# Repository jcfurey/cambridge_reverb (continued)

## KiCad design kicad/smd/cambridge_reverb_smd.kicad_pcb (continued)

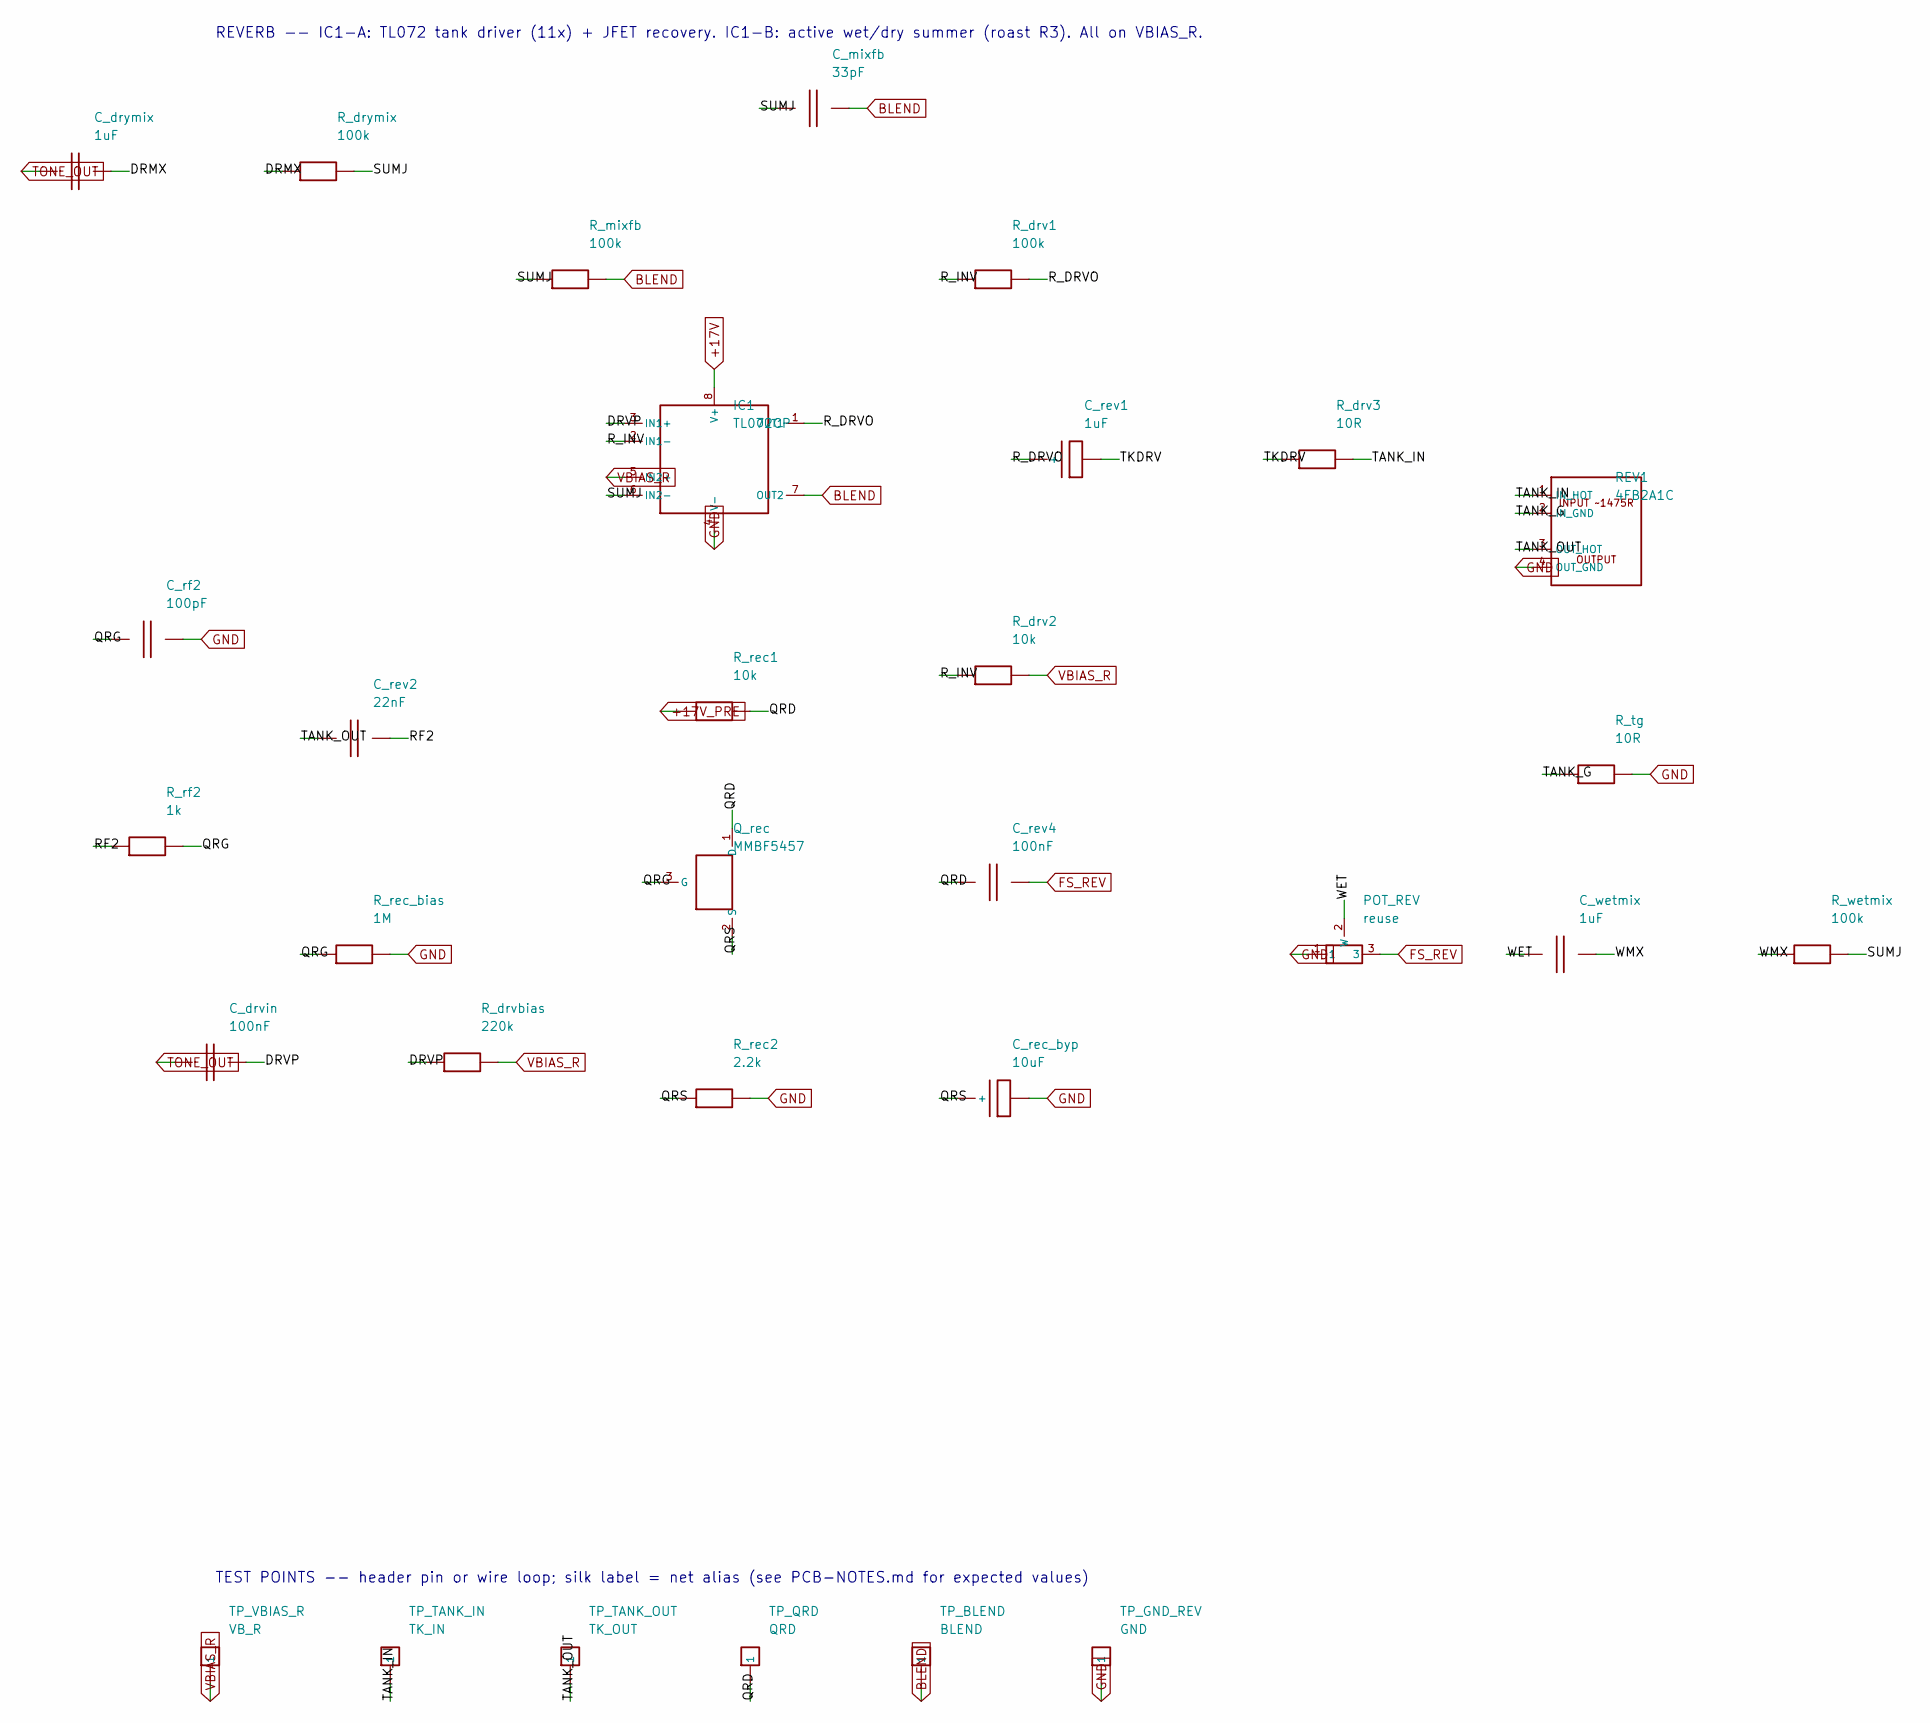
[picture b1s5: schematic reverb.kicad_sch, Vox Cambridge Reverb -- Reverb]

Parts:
C_drvin: 100nF; C_1206_3216Metric
C_drymix: 1uF; C_1206_3216Metric
C_mixfb: 33pF; C_0805_2012Metric
C_rec_byp: 10uF; CP_Radial_D5.0mm_P2.00mm
C_rev1: 1uF; CP_Radial_D5.0mm_P2.00mm
C_rev2: 22nF; C_1206_3216Metric
C_rev4: 100nF; C_1206_3216Metric
C_rf2: 100pF; C_0805_2012Metric
C_wetmix: 1uF; C_1206_3216Metric
IC1: TL072CP; DIP-8_W7.62mm
POT_REV: reuse; WirePad_1x03_P2.54mm_D1.2mm
Q_rec: MMBF5457; SOT-23
REV1: 4FB2A1C; WirePad_1x04_P2.54mm_D1.2mm
R_drv1: 100k; R_0805_2012Metric
R_drv2: 10k; R_0805_2012Metric
R_drv3: 10R; R_0805_2012Metric
R_drvbias: 220k; R_0805_2012Metric
R_drymix: 100k; R_0805_2012Metric
R_mixfb: 100k; R_0805_2012Metric
R_rec1: 10k; R_0805_2012Metric
R_rec2: 2.2k; R_Axial_DIN0207_L6.3mm_D2.5mm_P5.08mm_Vertical
R_rec_bias: 1M; R_0805_2012Metric
R_rf2: 1k; R_0805_2012Metric
R_tg: 10R; R_0805_2012Metric
R_wetmix: 100k; R_0805_2012Metric
TP_BLEND: BLEND; TestPoint_THT_D2.0mm_Label
TP_GND_REV: GND; TestPoint_THT_D2.0mm_Label
TP_QRD: QRD; TestPoint_THT_D2.0mm_Label
TP_TANK_IN: TK_IN; TestPoint_THT_D2.0mm_Label
TP_TANK_OUT: TK_OUT; TestPoint_THT_D2.0mm_Label
TP_VBIAS_R: VB_R; TestPoint_THT_D2.0mm_Label

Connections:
+17V: IC1.8 (V+); also elsewhere on the board
+17V_PRE: R_rec1.1; also elsewhere on the board
BLEND: C_mixfb.2, IC1.7 (OUT2), R_mixfb.2, TP_BLEND.1; also elsewhere on the board
DRMX: C_drymix.2, R_drymix.1
DRVP: C_drvin.2, IC1.3 (IN1+), R_drvbias.1
FS_REV: C_rev4.2, POT_REV.3; also elsewhere on the board
GND: C_rec_byp.2, C_rf2.2, IC1.4 (V-), POT_REV.1, REV1.4 (OUT_GND), R_rec2.2, R_rec_bias.2, R_tg.2, TP_GND_REV.1; also elsewhere on the board
QRD: C_rev4.1, Q_rec.1 (D), R_rec1.2, TP_QRD.1
QRG: C_rf2.1, Q_rec.3 (G), R_rec_bias.1, R_rf2.2
QRS: C_rec_byp.1 (+), Q_rec.2 (S), R_rec2.1
RF2: C_rev2.2, R_rf2.1
R_DRVO: C_rev1.1 (+), IC1.1 (OUT1), R_drv1.2
R_INV: IC1.2 (IN1-), R_drv1.1, R_drv2.1
SUMJ: C_mixfb.1, IC1.6 (IN2-), R_drymix.2, R_mixfb.1, R_wetmix.2
TANK_G: REV1.2 (IN_GND), R_tg.1
TANK_IN: REV1.1 (IN_HOT), R_drv3.2, TP_TANK_IN.1
TANK_OUT: C_rev2.1, REV1.3 (OUT_HOT), TP_TANK_OUT.1
TKDRV: C_rev1.2, R_drv3.1
TONE_OUT: C_drvin.1, C_drymix.1; also elsewhere on the board
VBIAS_R: IC1.5 (IN2+), R_drv2.2, R_drvbias.2, TP_VBIAS_R.1; also elsewhere on the board
WET: C_wetmix.1, POT_REV.2 (W)
WMX: C_wetmix.2, R_wetmix.1

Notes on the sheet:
REVERB -- IC1-A: TL072 tank driver (11x) + JFET recovery. IC1-B: active wet/dry summer (roast R3). All on VBIAS_R.
TEST POINTS -- header pin or wire loop; silk label = net alias (see PCB-NOTES.md for expected values)

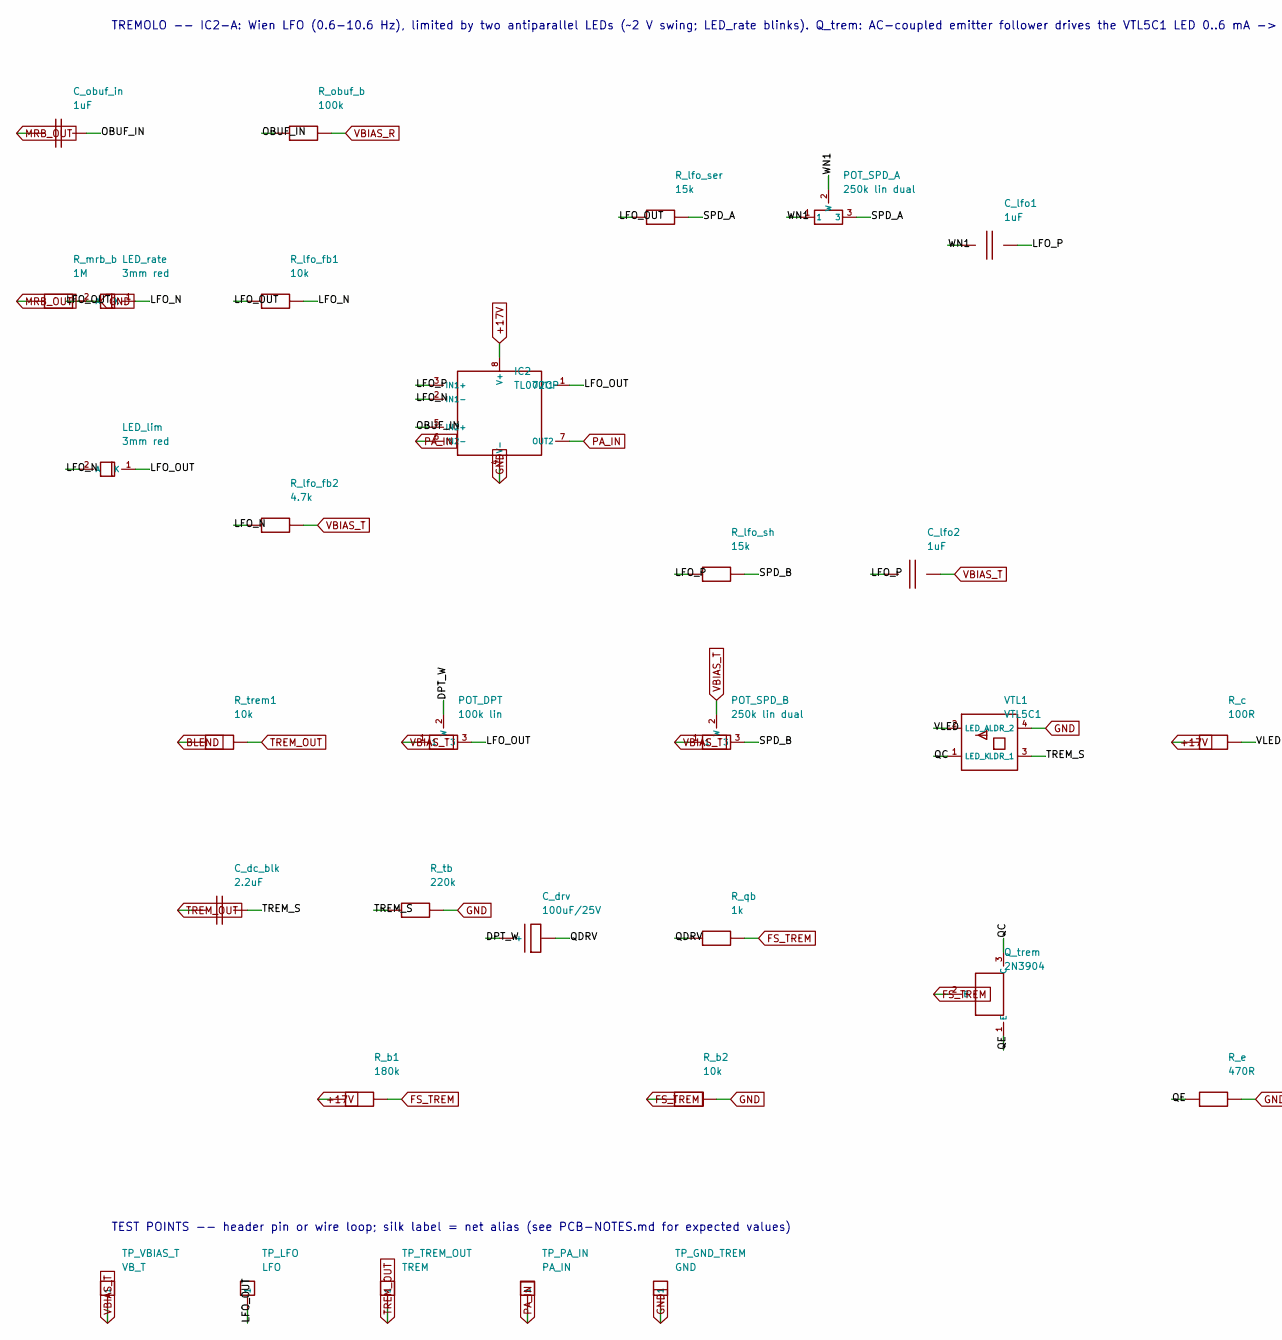
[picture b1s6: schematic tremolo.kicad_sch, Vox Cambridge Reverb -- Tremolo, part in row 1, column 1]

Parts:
C_dc_blk: 2.2uF; C_1206_3216Metric
C_drv: 100uF/25V; CP_Radial_D6.3mm_P2.50mm
C_lfo1, C_lfo2: 1uF; C_1206_3216Metric
C_obuf_in: 1uF; C_1206_3216Metric
IC2: TL072CP; DIP-8_W7.62mm
LED_lim: 3mm red; LED_D3.0mm
LED_rate: 3mm red; LED_D3.0mm
POT_DPT: 100k lin; WirePad_1x03_P2.54mm_D1.2mm
POT_SPD_A: 250k lin dual; WirePad_1x03_P2.54mm_D1.2mm
POT_SPD_B: 250k lin dual; WirePad_1x03_P2.54mm_D1.2mm
Q_trem: 2N3904; SOT-23_MMBT3904_as_EBC
R_b1: 180k; R_0805_2012Metric
R_b2: 10k; R_0805_2012Metric
R_c: 100R; R_0805_2012Metric
R_e: 470R; R_0805_2012Metric
R_lfo_fb1: 10k; R_0805_2012Metric
R_lfo_fb2: 4.7k; R_0805_2012Metric
R_lfo_ser: 15k; R_0805_2012Metric
R_lfo_sh: 15k; R_0805_2012Metric
R_mrb_b: 1M; R_0805_2012Metric
R_obuf_b: 100k; R_0805_2012Metric
R_qb: 1k; R_0805_2012Metric
R_tb: 220k; R_0805_2012Metric
R_trem1: 10k; R_0805_2012Metric
TP_GND_TREM: GND; TestPoint_THT_D2.0mm_Label
TP_LFO: LFO; TestPoint_THT_D2.0mm_Label
TP_PA_IN: PA_IN; TestPoint_THT_D2.0mm_Label
TP_TREM_OUT: TREM; TestPoint_THT_D2.0mm_Label
TP_VBIAS_T: VB_T; TestPoint_THT_D2.0mm_Label
VTL1: VTL5C1

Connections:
+17V: IC2.8 (V+), R_b1.1, R_c.1; also elsewhere on the board
BLEND: R_trem1.1; also elsewhere on the board
DPT_W: C_drv.1 (+), POT_DPT.2 (W)
FS_TREM: Q_trem.2 (B), R_b1.2, R_b2.1, R_qb.2; also elsewhere on the board
GND: IC2.4 (V-), R_b2.2, R_e.2, R_mrb_b.2, R_tb.2, TP_GND_TREM.1, VTL1.4 (LDR_2); also elsewhere on the board
LFO_N: IC2.2 (IN1-), LED_lim.2 (A), LED_rate.1 (K), R_lfo_fb1.2, R_lfo_fb2.1
LFO_OUT: IC2.1 (OUT1), LED_lim.1 (K), LED_rate.2 (A), POT_DPT.3, R_lfo_fb1.1, R_lfo_ser.1, TP_LFO.1
LFO_P: C_lfo1.2, C_lfo2.1, IC2.3 (IN1+), R_lfo_sh.1
MRB_OUT: C_obuf_in.1, R_mrb_b.1; also elsewhere on the board
OBUF_IN: C_obuf_in.2, IC2.5 (IN2+), R_obuf_b.1
PA_IN: IC2.6 (IN2-), IC2.7 (OUT2), TP_PA_IN.1; also elsewhere on the board
QC: Q_trem.3 (C), VTL1.1 (LED_K)
QDRV: C_drv.2, R_qb.1
QE: Q_trem.1 (E), R_e.1
SPD_A: POT_SPD_A.3, R_lfo_ser.2
SPD_B: POT_SPD_B.3, R_lfo_sh.2
TREM_OUT: C_dc_blk.1, R_trem1.2, TP_TREM_OUT.1; also elsewhere on the board
TREM_S: C_dc_blk.2, R_tb.1, VTL1.3 (LDR_1)
VBIAS_R: R_obuf_b.2; also elsewhere on the board
VBIAS_T: C_lfo2.2, POT_DPT.1, POT_SPD_B.1, POT_SPD_B.2 (W), R_lfo_fb2.2, TP_VBIAS_T.1; also elsewhere on the board
VLED: R_c.2, VTL1.2 (LED_A)
WN1: C_lfo1.1, POT_SPD_A.1, POT_SPD_A.2 (W)

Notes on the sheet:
TREMOLO -- IC2-A: Wien LFO (0.6-10.6 Hz), limited by two antiparallel LEDs (~2 V swing; LED_rate blinks). Q_trem: AC-coupled emitter follower drives the VTL5C1 LED 0..6 mA -> 15 dB depth, 0.8 dB insertion loss (was 7 mA DC: -20 dB pad, 1.7 dB depth). IC2-B: post-MRB output buffer -> PA_IN.
TEST POINTS -- header pin or wire loop; silk label = net alias (see PCB-NOTES.md for expected values)

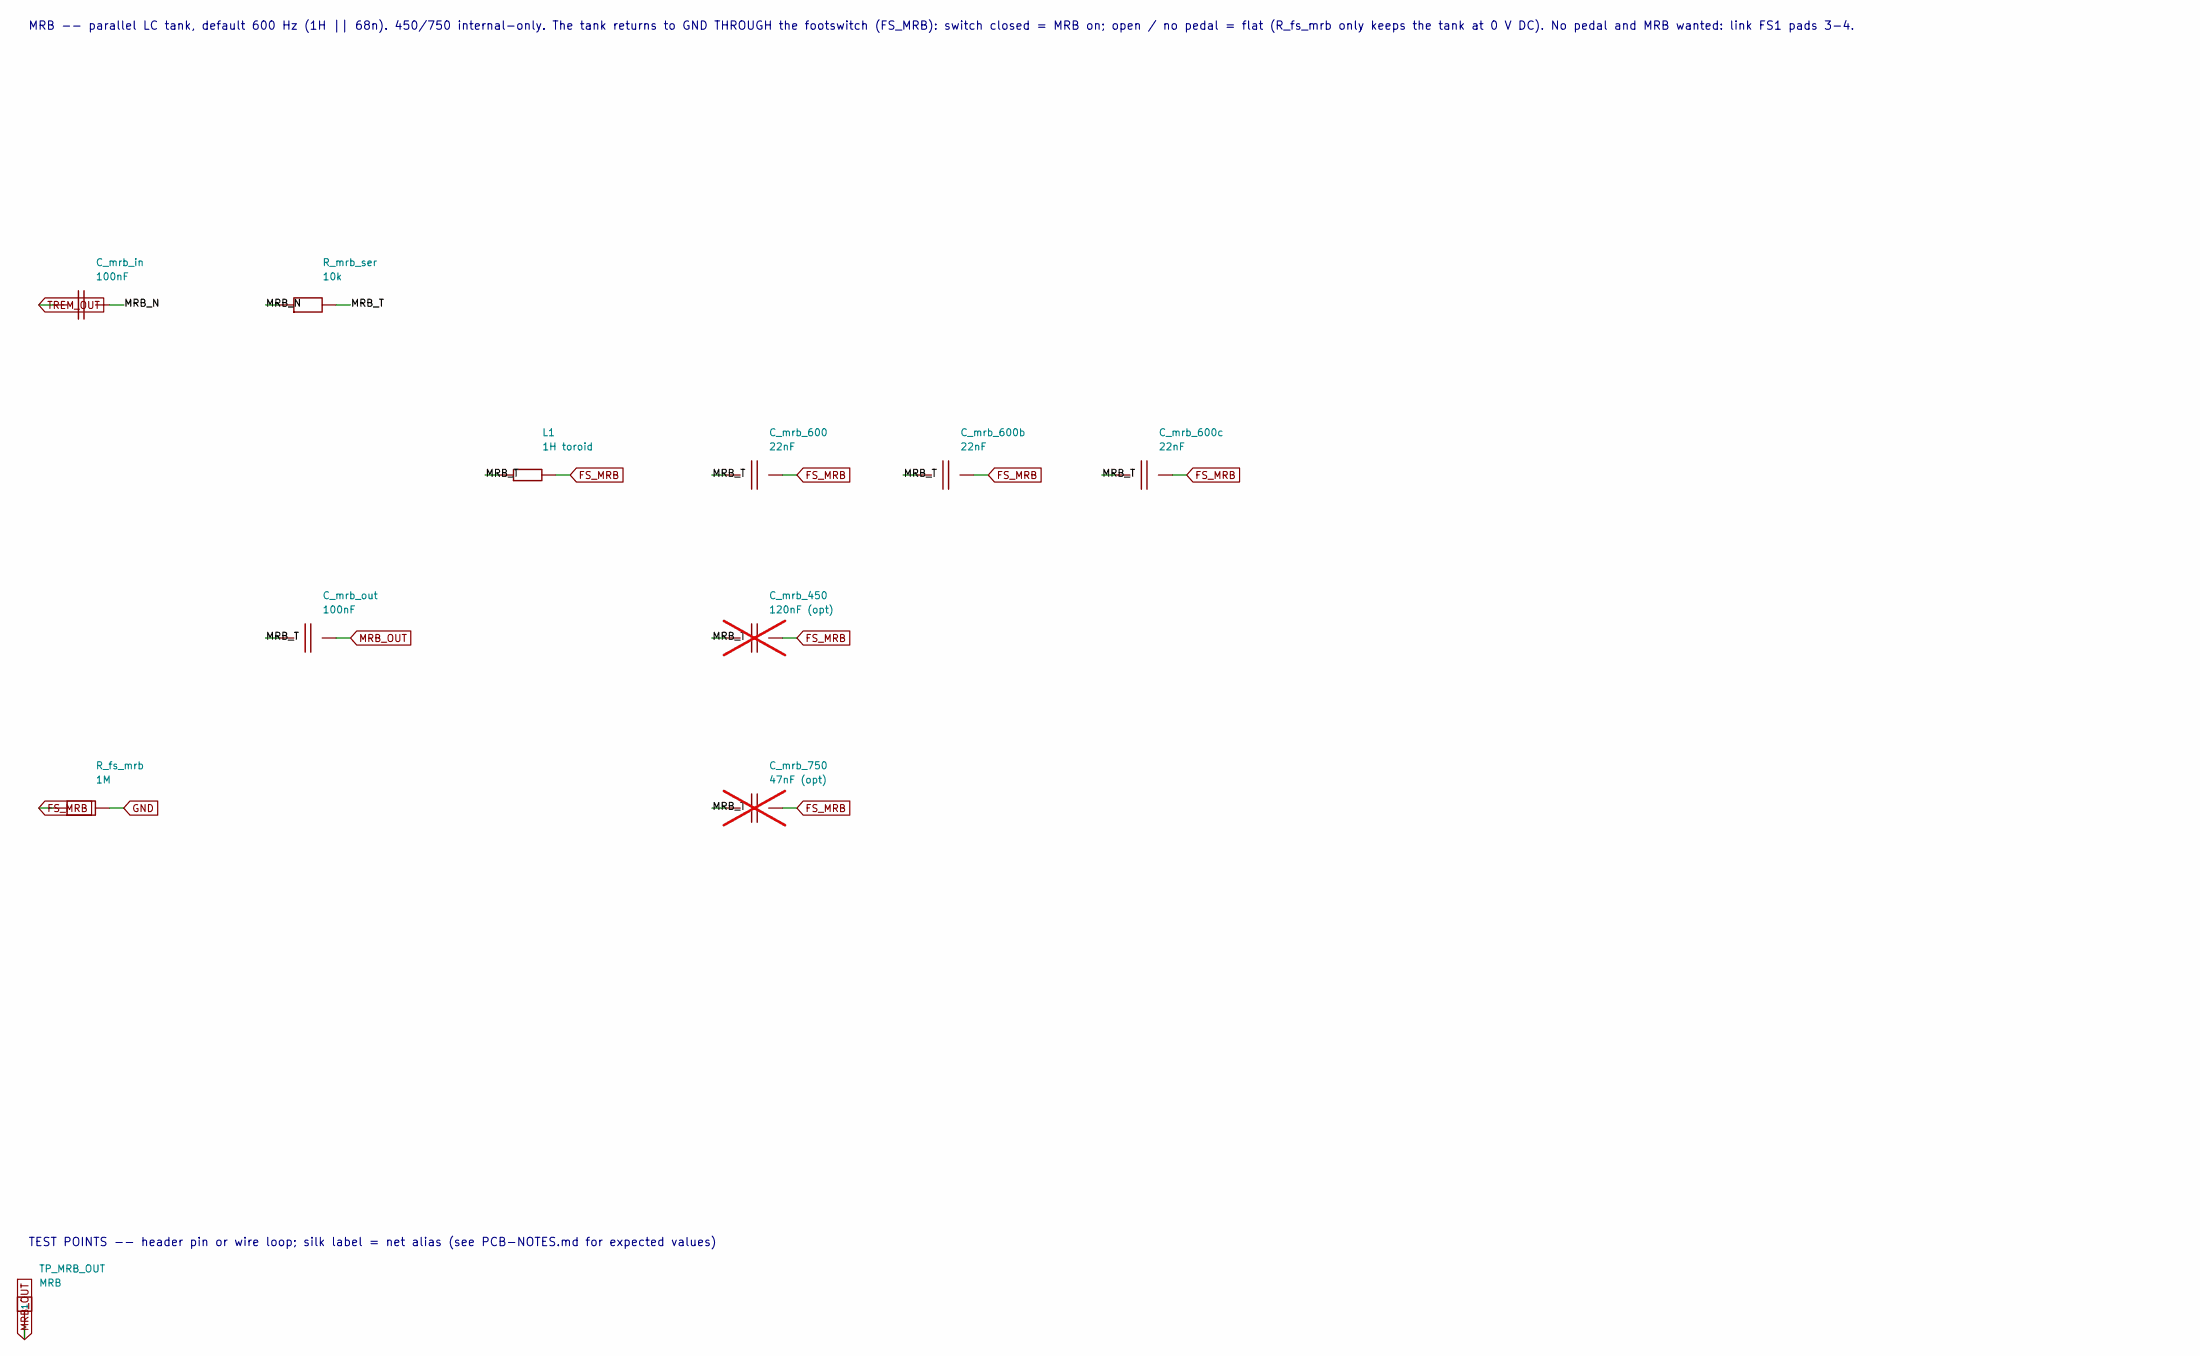
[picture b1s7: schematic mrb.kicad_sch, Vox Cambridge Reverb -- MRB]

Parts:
C_mrb_450: 120nF (opt); C_1206_3216Metric; not fitted
C_mrb_600, C_mrb_600b, C_mrb_600c: 22nF; C_1206_3216Metric
C_mrb_750: 47nF (opt); C_1206_3216Metric; not fitted
C_mrb_in: 100nF; C_1206_3216Metric
C_mrb_out: 100nF; C_1206_3216Metric
L1: 1H toroid; Inductor_MRB_1H_Toroid
R_fs_mrb: 1M; R_0805_2012Metric
R_mrb_ser: 10k; R_0805_2012Metric
TP_MRB_OUT: MRB; TestPoint_THT_D2.0mm_Label

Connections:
FS_MRB: C_mrb_450.2, C_mrb_600.2, C_mrb_600b.2, C_mrb_600c.2, C_mrb_750.2, L1.2, R_fs_mrb.1; also elsewhere on the board
GND: R_fs_mrb.2; also elsewhere on the board
MRB_N: C_mrb_in.2, R_mrb_ser.1
MRB_OUT: C_mrb_out.2, TP_MRB_OUT.1; also elsewhere on the board
MRB_T: C_mrb_450.1, C_mrb_600.1, C_mrb_600b.1, C_mrb_600c.1, C_mrb_750.1, C_mrb_out.1, L1.1, R_mrb_ser.2
TREM_OUT: C_mrb_in.1; also elsewhere on the board

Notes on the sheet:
MRB -- parallel LC tank, default 600 Hz (1H || 68n). 450/750 internal-only. The tank returns to GND THROUGH the footswitch (FS_MRB): switch closed = MRB on; open / no pedal = flat (R_fs_mrb only keeps the tank at 0 V DC). No pedal and MRB wanted: link FS1 pads 3-4.
TEST POINTS -- header pin or wire loop; silk label = net alias (see PCB-NOTES.md for expected values)

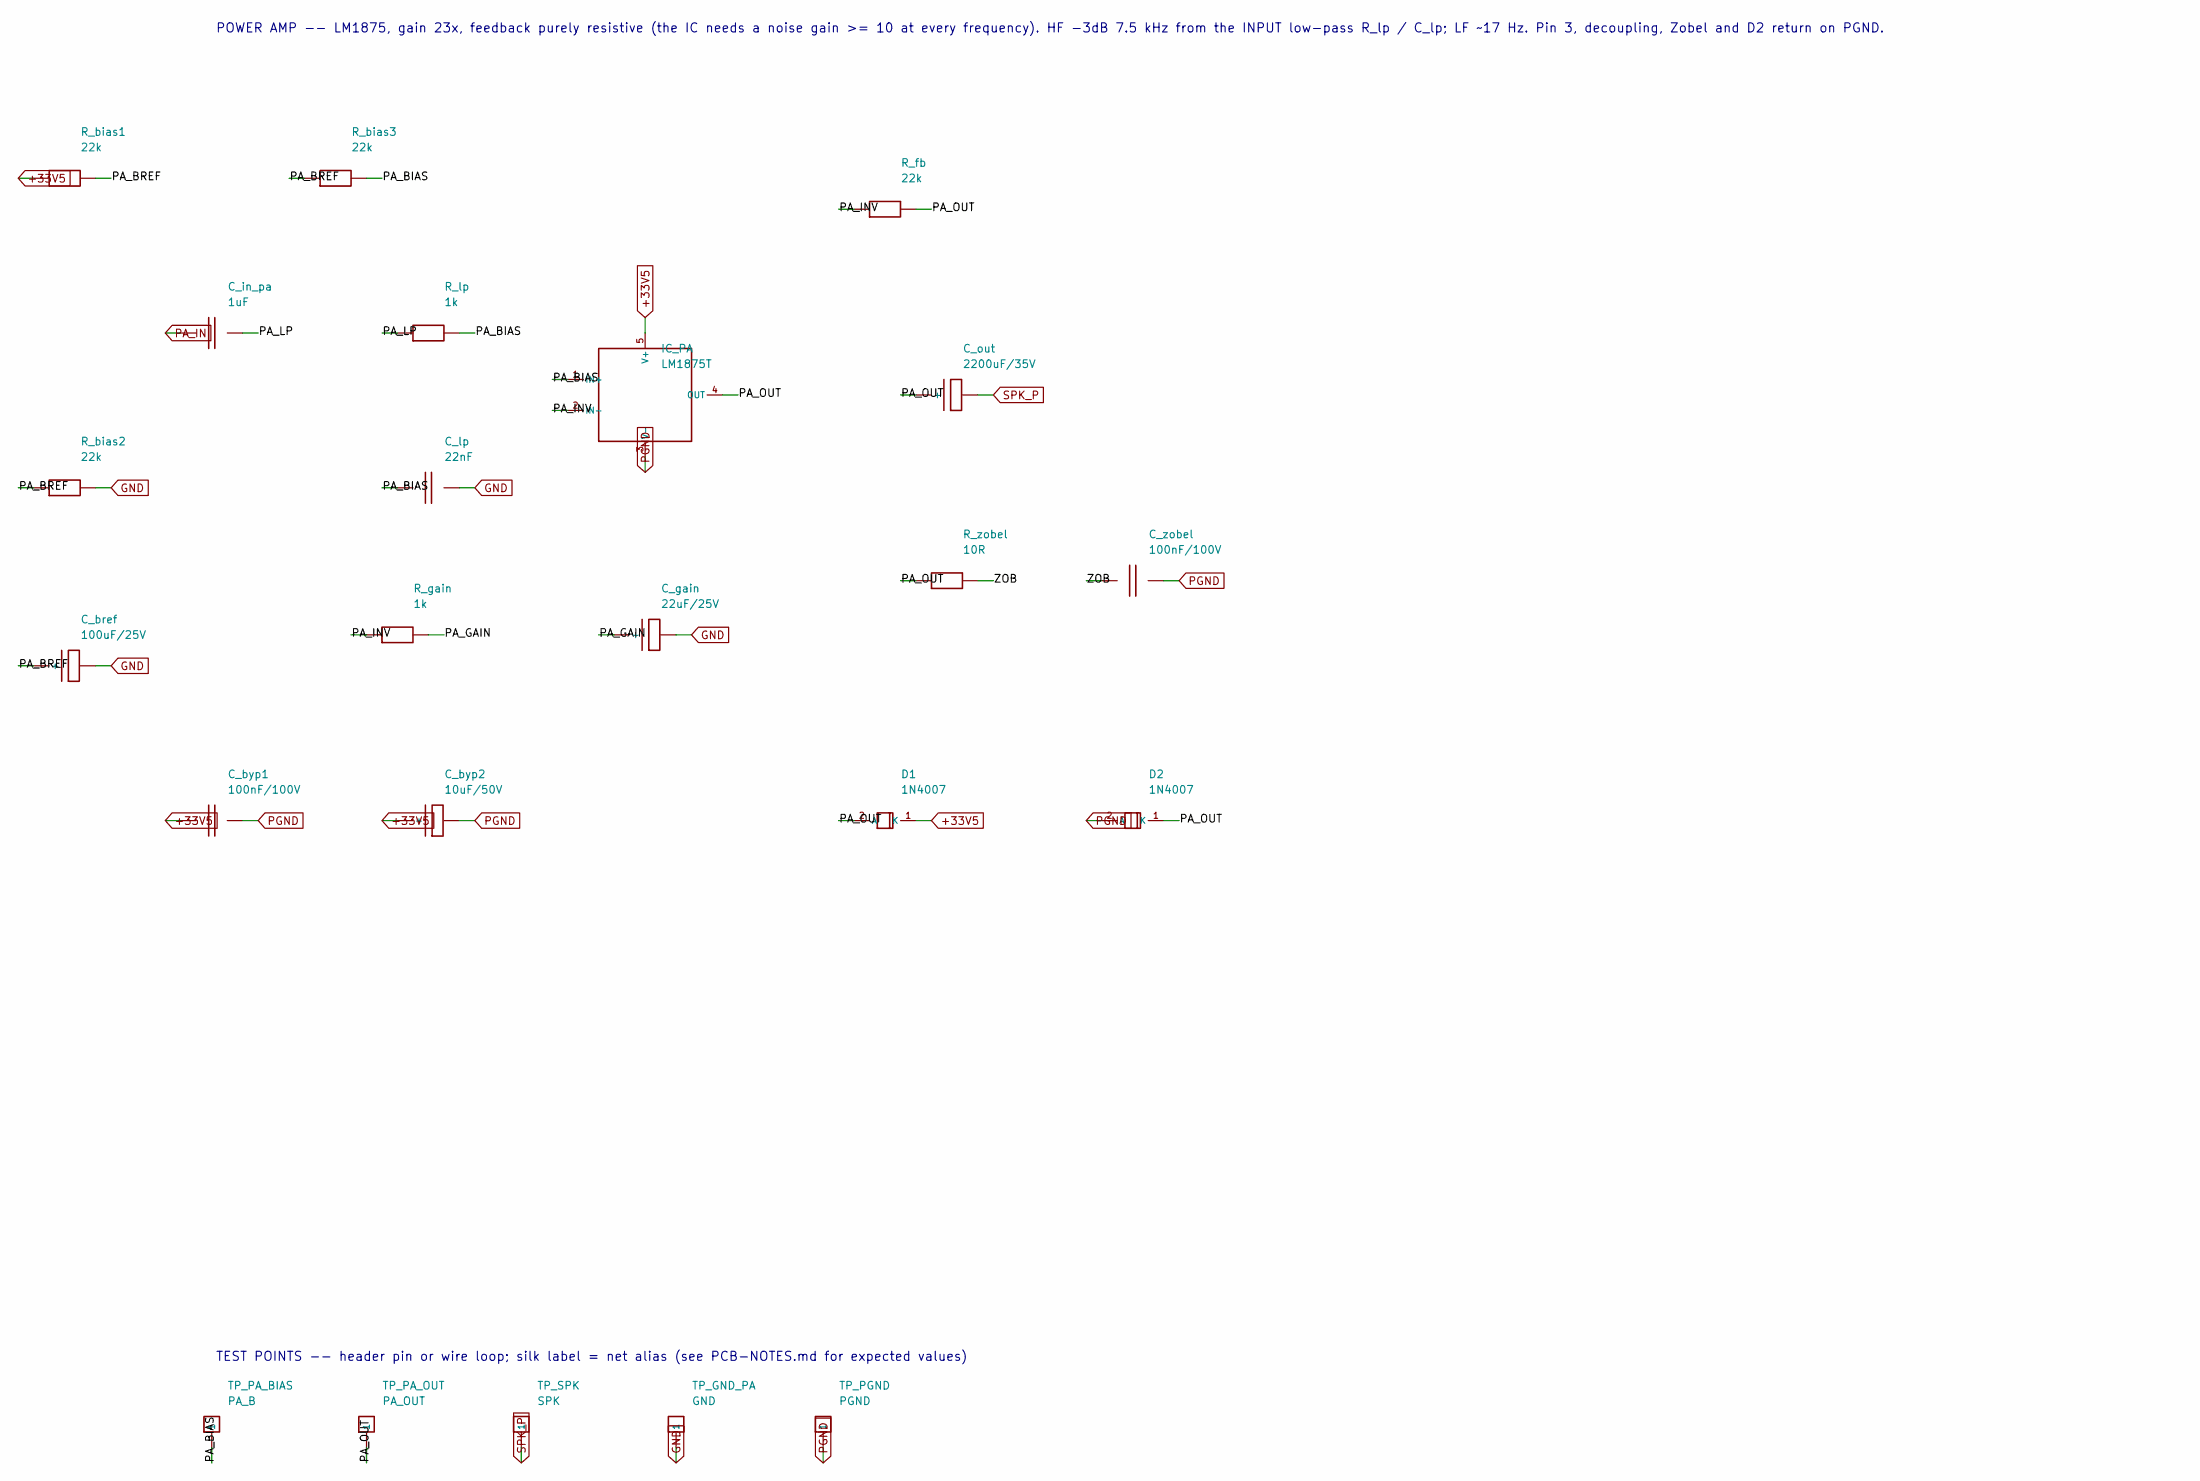
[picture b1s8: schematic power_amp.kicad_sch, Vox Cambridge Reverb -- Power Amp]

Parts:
C_bref: 100uF/25V; CP_Radial_D6.3mm_P2.50mm
C_byp1: 100nF/100V; C_0805_2012Metric
C_byp2: 10uF/50V; CP_Radial_D5.0mm_P2.00mm
C_gain: 22uF/25V; CP_Radial_D5.0mm_P2.00mm
C_in_pa: 1uF; C_1206_3216Metric
C_lp: 22nF; C_1206_3216Metric
C_out: 2200uF/35V; CP_Radial_D16.0mm_P7.50mm
C_zobel: 100nF/100V; C_0805_2012Metric
D1, D2: 1N4007; D_SMA
IC_PA: LM1875T; TO-220-5_Vertical_P1.70mm_LM1875
R_bias1, R_bias2, R_bias3: 22k; R_0805_2012Metric
R_fb: 22k; R_0805_2012Metric
R_gain: 1k; R_0805_2012Metric
R_lp: 1k; R_0805_2012Metric
R_zobel: 10R; R_Axial_DIN0207_L6.3mm_D2.5mm_P5.08mm_Vertical
TP_GND_PA: GND; TestPoint_THT_D2.0mm_Label
TP_PA_BIAS: PA_B; TestPoint_THT_D2.0mm_Label
TP_PA_OUT: PA_OUT; TestPoint_THT_D2.0mm_Label
TP_PGND: PGND; TestPoint_THT_D2.0mm_Label
TP_SPK: SPK; TestPoint_THT_D2.0mm_Label

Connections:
+33V5: C_byp1.1, C_byp2.1 (+), D1.1 (K), IC_PA.5 (V+), R_bias1.1; also elsewhere on the board
GND: C_bref.2, C_gain.2, C_lp.2, R_bias2.2, TP_GND_PA.1; also elsewhere on the board
PA_BIAS: C_lp.1, IC_PA.1 (IN+), R_bias3.2, R_lp.2, TP_PA_BIAS.1
PA_BREF: C_bref.1 (+), R_bias1.2, R_bias2.1, R_bias3.1
PA_GAIN: C_gain.1 (+), R_gain.2
PA_IN: C_in_pa.1; also elsewhere on the board
PA_INV: IC_PA.2 (IN-), R_fb.1, R_gain.1
PA_LP: C_in_pa.2, R_lp.1
PA_OUT: C_out.1 (+), D1.2 (A), D2.1 (K), IC_PA.4 (OUT), R_fb.2, R_zobel.1, TP_PA_OUT.1
PGND: C_byp1.2, C_byp2.2, C_zobel.2, D2.2 (A), IC_PA.3 (V-), TP_PGND.1; also elsewhere on the board
SPK_P: C_out.2, TP_SPK.1; also elsewhere on the board
ZOB: C_zobel.1, R_zobel.2

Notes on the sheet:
POWER AMP -- LM1875, gain 23x, feedback purely resistive (the IC needs a noise gain >= 10 at every frequency). HF -3dB 7.5 kHz from the INPUT low-pass R_lp / C_lp; LF ~17 Hz. Pin 3, decoupling, Zobel and D2 return on PGND.
TEST POINTS -- header pin or wire loop; silk label = net alias (see PCB-NOTES.md for expected values)

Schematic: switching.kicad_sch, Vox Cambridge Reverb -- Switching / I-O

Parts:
FS1: DIN-6; WirePad_1x06_P2.54mm_D1.2mm
J_IN1: Input 1; WirePad_1x02_P2.54mm_D1.2mm
J_IN2: Input 2; WirePad_1x02_P2.54mm_D1.2mm
J_IN3: IN3 / FX return; WirePad_1x02_P2.54mm_D1.2mm
LS1: 10in Bulldog; WirePad_1x02_P5.08mm_D1.5mm
R_gnd: 0R; R_0805_2012Metric
R_spk_rtn: 0R; R_Axial_DIN0414_L11.9mm_D4.5mm_P15.24mm_Horizontal

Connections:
FS_MRB: FS1.3 (FS_MRB); also elsewhere on the board
FS_REV: FS1.1 (FS_REV); also elsewhere on the board
FS_TREM: FS1.2 (FS_TREM); also elsewhere on the board
FX_RET: J_IN3.1 (T); also elsewhere on the board
GND: FS1.4 (FS_GND), FS1.5 (NC5), FS1.6 (NC6), J_IN1.2 (S), J_IN2.2 (S), J_IN3.2 (S), R_gnd.2; also elsewhere on the board
GUITAR_IN: J_IN1.1 (T), J_IN2.1 (T); also elsewhere on the board
PGND: R_spk_rtn.2; also elsewhere on the board
SPK_N: LS1.2 (-), R_gnd.1, R_spk_rtn.1
SPK_P: LS1.1 (+); also elsewhere on the board

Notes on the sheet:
SWITCHING / I-O -- input jacks (IN3=internal FX loop), footswitch DIN, speaker.

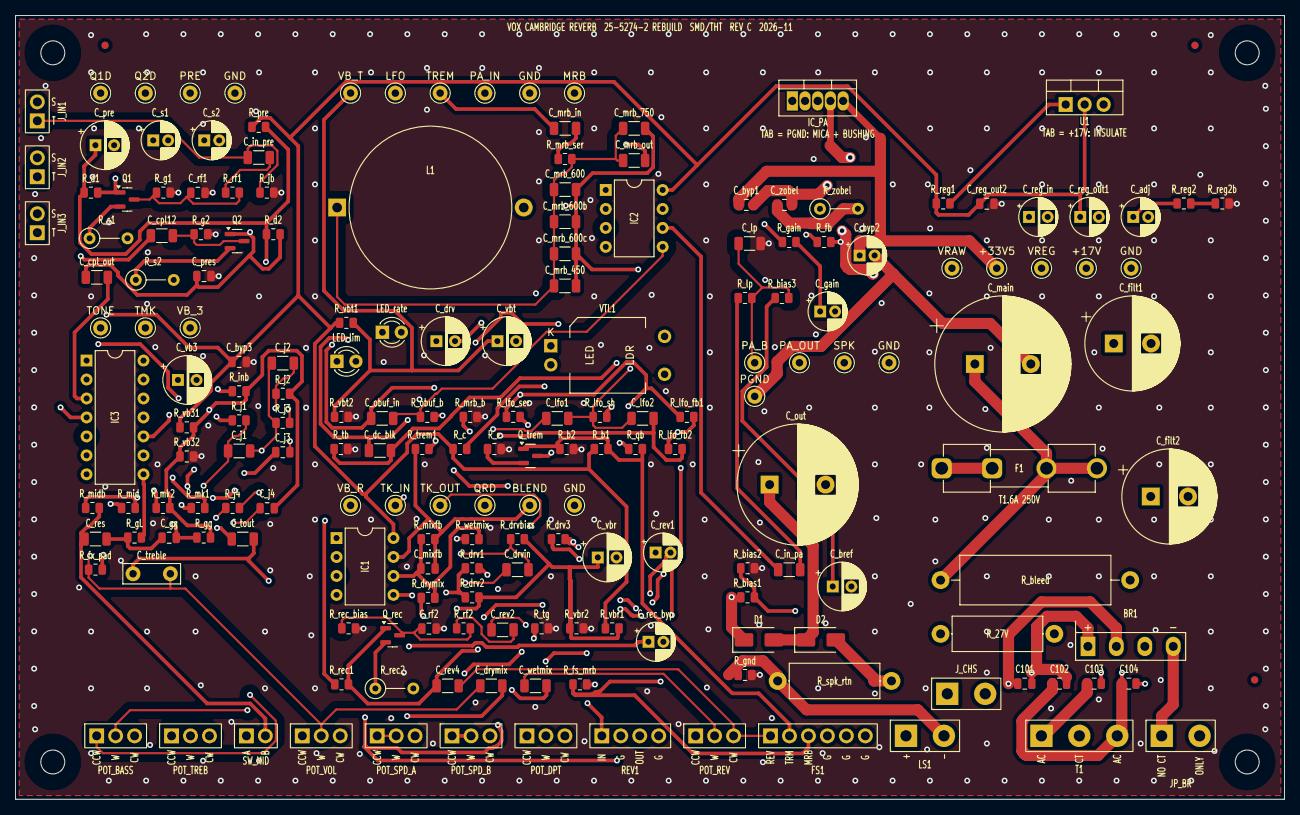
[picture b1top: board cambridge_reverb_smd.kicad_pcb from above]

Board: 4 copper layers, 170.0 x 105.0 mm, 198 parts (0 on the bottom side), 89 nets.

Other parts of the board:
FID1, FID2, FID3: Fiducial_1mm_Mask2mm
H1, H2, H3, H4: MountingHole_3.2mm_M3

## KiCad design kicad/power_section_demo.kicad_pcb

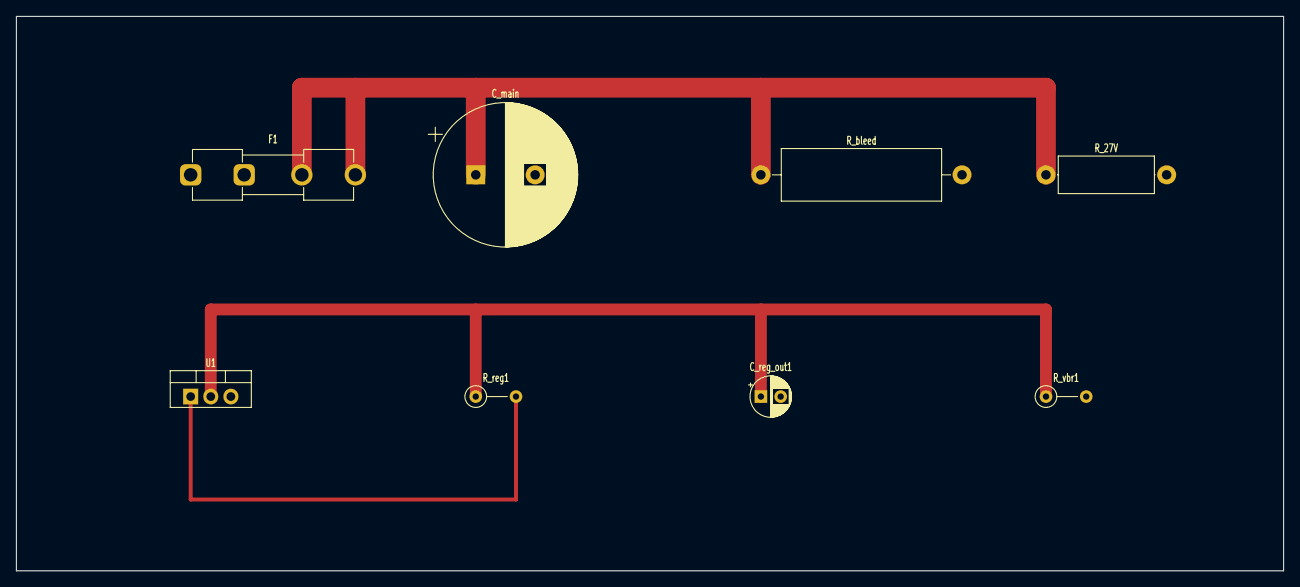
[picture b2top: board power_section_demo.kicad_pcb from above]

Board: 2 copper layers, 160.0 x 70.0 mm, 8 parts (0 on the bottom side), 5 nets.

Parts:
C_main: 4700uF/50V; CP_Radial_D18.0mm_P7.50mm
C_reg_out1: 10uF/25V; CP_Radial_D5.0mm_P2.50mm
F1: T1.6A; Fuseholder_Clip-5x20mm_Eaton_1A5601-01_Inline_P20.80x6.76mm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
R_27V: 100R/1W; R_Axial_DIN0414_L11.9mm_D4.5mm_P15.24mm_Horizontal
R_bleed: 10k/5W; R_Axial_Power_L20.0mm_W6.4mm_P25.40mm
R_reg1: 240R; R_Axial_DIN0207_L6.3mm_D2.5mm_P5.08mm_Vertical
R_vbr1: 100k; R_Axial_DIN0207_L6.3mm_D2.5mm_P5.08mm_Vertical
U1: LM317T; TO-220-3_Vertical

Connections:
+17V: C_reg_out1.1, R_reg1.1, R_vbr1.1, U1.2
+33V5: C_main.1, F1.2, R_27V.1, R_bleed.1
ADJ17: R_reg1.2, U1.1
GND: C_reg_out1.2, R_bleed.2
VREG_IN: R_27V.2, U1.3

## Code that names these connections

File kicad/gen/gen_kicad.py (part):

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 "MRB_OUT","FX_RET","VBIAS_R","VBIAS_T","FS_REV","FS_TREM","FS_MRB",
}
# FS_REV/FS_TREM/FS_MRB are the footswitch lines. Each pedal switch closes its line to
# GND (DIN pins 4-6): FS_REV shorts the reverb-recovery output (reverb off), FS_TREM
# shorts the tremolo LED driver's base (tremolo off), FS_MRB completes the MRB tank's
# ground return (MRB ON). With no pedal plugged in: reverb and tremolo follow their
# panel pots and the MRB is out of circuit (errata #27; until 2026-11 the three lines
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    # Until 2026-11 that pin was tied to GND as well, which shorts each half-winding through
    # a "-" diode on alternate half-cycles (errata #26). It now ends on its own net BR_NEG,
    # and JP_BR links it to GND ONLY for a transformer with a single winding and no tap.
    s.comp("BRIDGE","BR1","KBP410G",80,60,{"1":"VRAW","2":"AC1","3":"AC2","4":"BR_NEG"})  # KBP pin order + ~ ~ -
    s.comp("LINK","JP_BR","no-CT link (opt)",80,100,{"1":"BR_NEG","2":"PGND"})   # OPEN for a centre-tapped T1 (default); fit for a single 24 V winding and leave the CT pad empty
    # F1 carries the charging PULSES, not the average: 1.1 A rms at full sine power, 1.5 A rms
    # clipped (ground_audit.py rectifier model) -- a T1A fuse sat above its rating there; T1.6A
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    s.comp("CP","C_vb3","47uF/25V",70,90,{"1":"VBIAS_3","2":"GND"})
    s.comp("C","C_byp3","100nF/100V",70,60,{"1":"+17V","2":"GND"})
    s.comp("OPAMP14","IC3","TL074CN",130,100,{"3":"PREAMP_OUT","2":"BUF","1":"BUF",       # A: input buffer (low-Z drive for the passive network)
                                               "5":"JOUT","6":"MKN","7":"MK_OUT",          # B: make-up gain 1 + R_mk1/R_mk2 = 2
                                               "10":"GYP","9":"GYO","8":"GYO",            # C: gyrator follower (simulated inductor)
                                               "12":"MID","13":"OBUF","14":"OBUF",        # D: output buffer
                                               "4":"+17V","11":"GND"})
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    # ---- Sheet 4: Reverb (netlist-notes sheet 4) ----
    s=Sheet("Reverb","reverb.kicad_sch"); sheets.append(s)
    s.note("REVERB -- IC1-A: TL072 tank driver (11x) + JFET recovery. IC1-B: active wet/dry summer (roast R3). All on VBIAS_R.",40,20)
    # IC1-A = tank driver (pins 1,2,3) ; IC1-B = wet/dry summing mixer (pins 5,6,7)
    s.comp("OPAMP8","IC1","TL072CP",110,80,{"3":"DRVP","2":"R_INV","1":"R_DRVO",
            "8":"+17V","4":"GND","5":"VBIAS_R","6":"SUMJ","7":"BLEND"})
    s.comp("C","C_drvin","100nF",40,165,{"1":"TONE_OUT","2":"DRVP"})   # AC couple in
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    # ---- Sheet 5: Tremolo (netlist-notes sheet 5) ----
    s=Sheet("Tremolo","tremolo.kicad_sch"); sheets.append(s)
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    # IC2-A = LFO (pins 1,2,3) ; IC2-B = output buffer (pins 5,6,7), follower to PA_IN
    s.comp("OPAMP8","IC2","TL072CP",110,90,{"3":"LFO_P","2":"LFO_N","1":"LFO_OUT",
            "8":"+17V","4":"GND","5":"OBUF_IN","6":"PA_IN","7":"PA_IN"})
    s.comp("C","C_obuf_in","1uF",30,40,{"1":"MRB_OUT","2":"OBUF_IN"})  # post-MRB into buffer
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
    # ---- Sheet 7: Power Amp (netlist-notes sheet 7, verbatim) ----
    s=Sheet("Power Amp","power_amp.kicad_sch"); sheets.append(s)
    s.note("POWER AMP -- LM1875, gain 23x, feedback purely resistive (the IC needs a noise gain >= 10 at every frequency). HF -3dB 7.5 kHz from the INPUT low-pass R_lp / C_lp; LF ~17 Hz. Pin 3, decoupling, Zobel and D2 return on PGND.",40,20)
    # The 7 kHz guitar roll-off is an RC in front of the + input. Until 2026-11 it was C_fb_hf,
    # 1 nF across R_fb: that takes the amplifier's noise gain from 23 down to 1 above ~160 kHz,
    # and the LM1875 is only compensated for gains of 10 or more (data sheet, "Stability") --
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    s.comp("CP","C_out","2200uF/35V",160,80,{"1":"PA_OUT","2":"SPK_P"})
    s.comp("D","D1","1N4007",150,150,{"2":"PA_OUT","1":"+33V5"})   # anode (2) on the output, cathode (1) on the rail
    s.comp("D","D2","1N4007",190,150,{"2":"PGND","1":"PA_OUT"})    # anode (2) on power ground, cathode (1) on the output
    s.comp("C","C_byp1","100nF/100V",40,150,{"1":"+33V5","2":"PGND"})   # pin 5 to pin 3, at the IC (gen_pcb CLOSE)
    s.comp("CP","C_byp2","10uF/50V",75,150,{"1":"+33V5","2":"PGND"})

    # ---- Sheet 8: Switching / I-O ----
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
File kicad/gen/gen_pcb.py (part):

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# 40 mm inverting-input node, and tank-drive nets (0.6 / 0.8 mm rules) that the routers
# could not always get across the column.
NEAR_BY_PROFILE = {
  "smd": {"IC1": ["R_mixfb", "C_mixfb", "R_drymix", "R_wetmix",      # summer: SUMJ / BLEND, pins 6 / 7
                  "R_drv1", "R_drv2", "R_drvbias", "C_drvin", "R_drv3"]},   # tank driver: pins 1-3
}
def configure(profile):
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    class clearance to the neighbouring pins -- the autorouter leaves exactly
    these unrouted. A hand layout necks the trace down at the pin; we do the same
    with a 0.9 mm stub per pin (0.9 mm of 1 oz copper carries the ~1.7 A peak with
    margin over a few mm): pin 4 (PA_OUT) straight down 6 mm, pin 5 (+33V5)
    fanned 5 mm right / 5 mm down, so the full-width traces attach to stub ends
    ~6.8 mm apart, clear of the pin row. Locked tracks export to the DSN as
    `(type fix)`, so Freerouting keeps them and connects to their far ends."""
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        return 0
    fp = fps["IC_PA"][1]
    n = 0
    # pin 3 (V-) is on the power ground PGND since errata #32 -- a routed net, not a pad in
    # the plane -- so it needs its own way out: straight down like pin 4, but on the INNER
    # signal layer, where nothing else leaves the pin row (4-layer boards only).
    stubs = [("4", 0.0, 6.0, pcbnew.F_Cu), ("5", 5.0, 5.0, pcbnew.F_Cu)]
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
